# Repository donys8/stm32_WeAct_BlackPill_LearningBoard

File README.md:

# Learning Board STM32 WeAct Blackpill V2
Repository ini berisi desain Learning Board untuk STM32 WeAct Blackpill V2. Learning board ini dirancang untuk memudahkan pembelajaran dan eksperimen dengan mikrokontroler STM32, khususnya varian Blackpill dari WeAct.

## Deskripsi
Proyek ini mencakup file desain yang meliputi:

.kicad_pro : File proyek utama KiCad.

.kicad_sch : Schematic desain rangkaian.

.kicad_pcb : Layout PCB.

## Requirement
KiCad versi 7.x atau yang lebih baru

## 3D Preview

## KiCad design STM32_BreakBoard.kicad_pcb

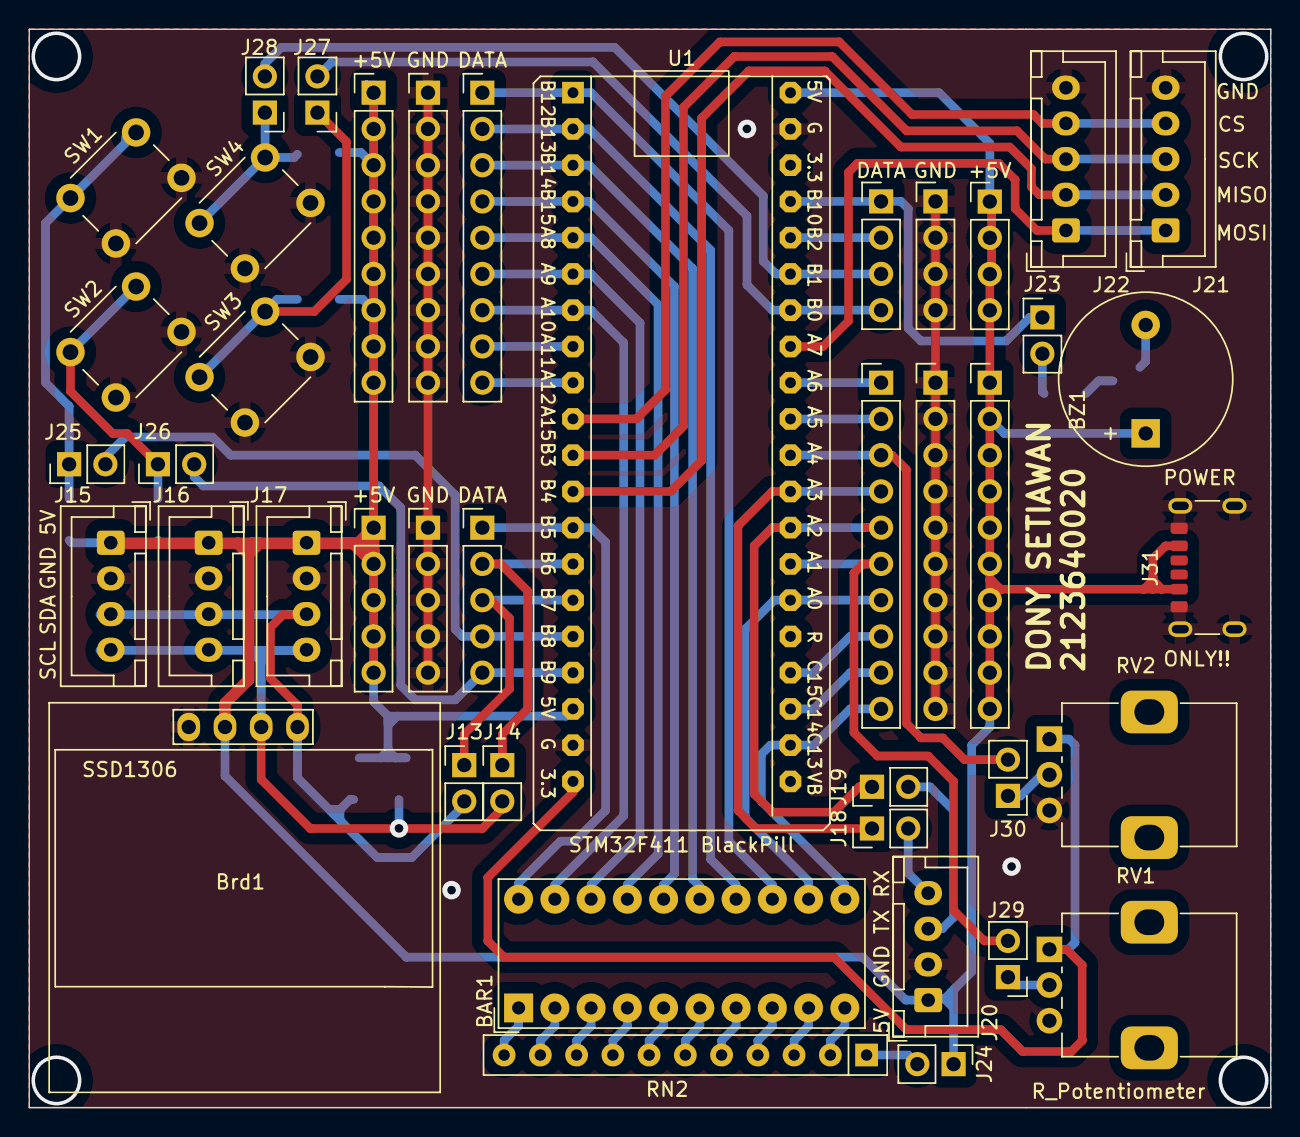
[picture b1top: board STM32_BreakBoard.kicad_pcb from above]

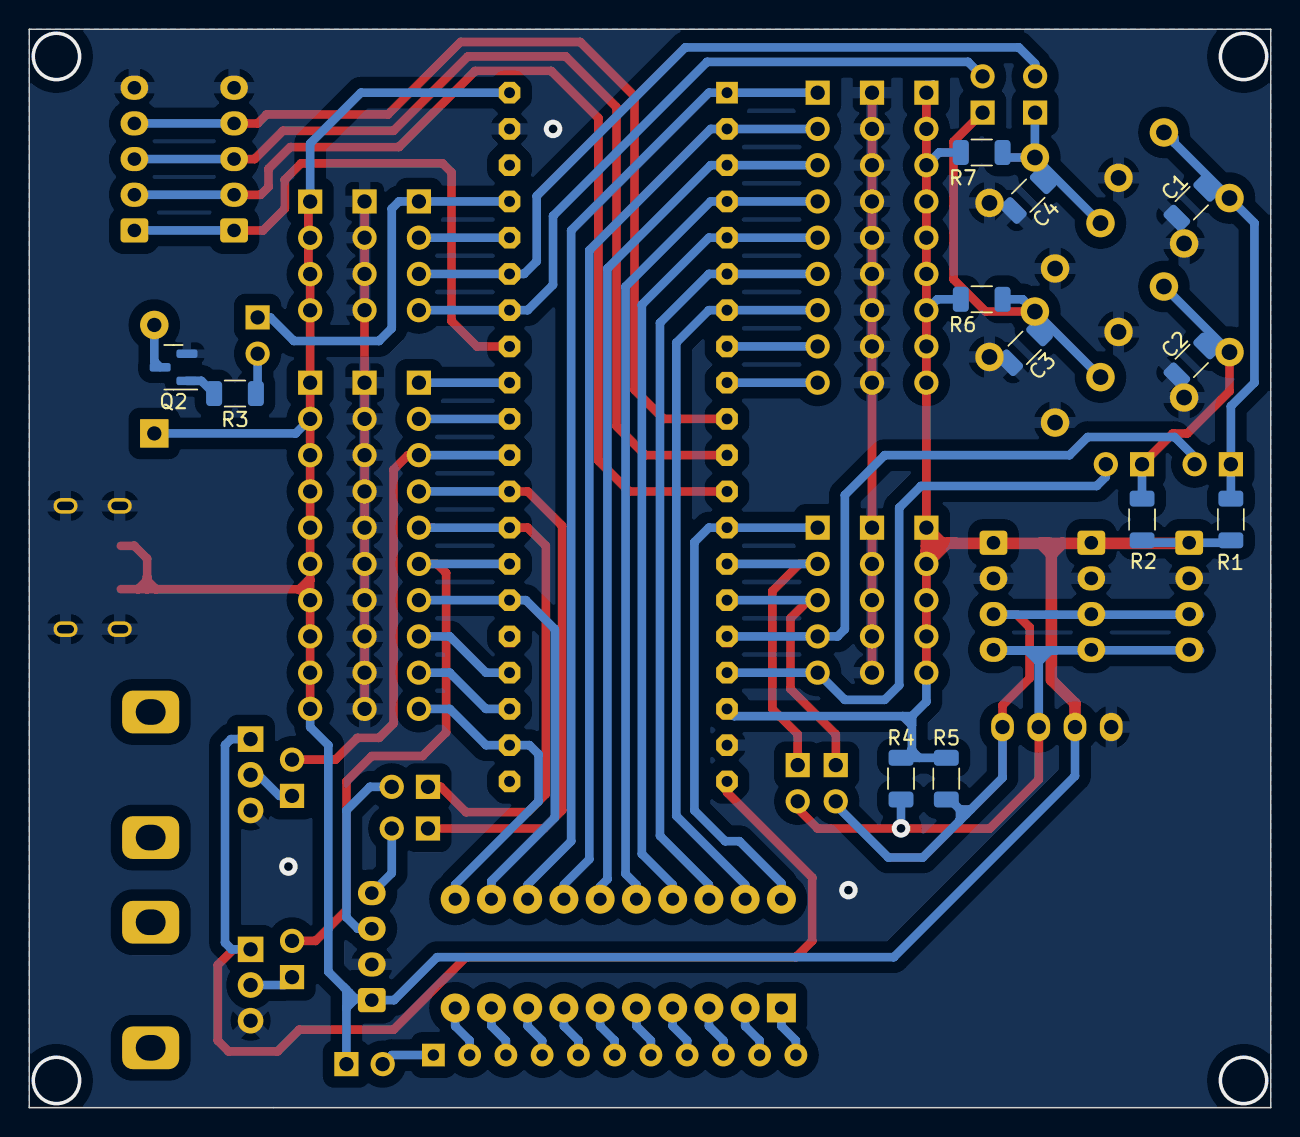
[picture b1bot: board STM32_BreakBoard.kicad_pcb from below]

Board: 2 copper layers, 87.0 x 75.6 mm, 54 parts (12 on the bottom side), 59 nets.

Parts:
BAR1: HDSP-4830_2; HDSP-4830
BZ1: Buzzer; Buzzer_12x9.5RM7.6
Brd1: SSD1306; 128x64OLED
C1, C2, C3, C4: C_Small; C_1206_3216Metric
J1: DATA; PinHeader_1x09_P2.54mm_Vertical
J2: DATA; PinHeader_1x05_P2.54mm_Vertical
J3: +5V; PinHeader_1x09_P2.54mm_Vertical
J4: +5V; PinHeader_1x05_P2.54mm_Vertical
J5: GND; PinHeader_1x09_P2.54mm_Vertical
J6: GND; PinHeader_1x05_P2.54mm_Vertical
J7: DATA; PinHeader_1x04_P2.54mm_Vertical
J8: DATA; PinHeader_1x10_P2.54mm_Vertical
J9: +5V; PinHeader_1x04_P2.54mm_Vertical
J10: +5V; PinHeader_1x10_P2.54mm_Vertical
J11: GND; PinHeader_1x04_P2.54mm_Vertical
J12: GND; PinHeader_1x10_P2.54mm_Vertical
J13, J14, J18, J19, J23, J24, J25, J26, J27, J28, J29, J30: Conn_01x02; PinHeader_1x02_P2.54mm_Vertical
J15, J16, J17, J20: Conn_01x04; JST_XH_B4B-XH-A_1x04_P2.50mm_Vertical
J21, J22: Conn_01x05; JST_XH_B5B-XH-A_1x05_P2.50mm_Vertical
J31: USB_C_Receptacle_PowerOnly_6P; USB_C_Receptacle_GCT_USB4125-xx-x_6P_TopMnt_Horizontal
Q2: Q_PMOS_GSD; SOT-23
R1, R2, R6, R7: 10k; R_1206_3216Metric
R3: 150; R_1206_3216Metric
R4, R5: 4k7; R_1206_3216Metric
RN2: R_Network10; R_Array_SIP11
RV1, RV2: R_Potentiometer; Potentiometer_Alps_RK09K_Single_Vertical
SW1, SW2, SW3, SW4: SW_Push_Dual; SW_PUSH_6mm
U1: STM32F411 BlackPill; STM32F411_Black_Pill

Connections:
+3V3: RV1.1, RV2.1, U1.20 (3.3V)
+5V: BZ1.1 (-), Brd1.2 (VCC), J3.1, J3.2, J3.3, J3.4, J3.5, J3.6, J3.7, J3.8, J3.9, J4.1, J4.2, J4.3, J4.4, J4.5, J9.1, J9.2, J9.3, J9.4, J10.1, J10.2, J10.3, J10.4, J10.5, J10.6, J10.7, J10.8, J10.9, J10.10, J15.1, J16.1, J17.1, J20.1, J24.1, J31.A9 (VBUS), J31.B9 (VBUS), R1.1, R2.1, R4.1, R5.1, R6.1, R7.1, U1.18 (5V), U1.40 (5V)
A0: BAR1.12 (K), J8.7, U1.26 (A0)
A1: J8.6, J29.2, U1.27 (A1)
A2: J8.5, J19.1, U1.28 (A2)
A3: J8.4, J18.1, U1.29 (A3)
A4: J8.3, J30.2, U1.30 (A4)
A5: J8.2, U1.31 (A5)
A6: J8.1, U1.32 (A6)
A7: J21.1, J22.1, U1.33 (A7)
A8: BAR1.17 (K), J1.5, U1.5 (A8)
A9: BAR1.18 (K), J1.6, U1.6 (A9)
A10: BAR1.19 (K), J1.7, U1.7 (A10)
A11: J1.8, U1.8 (A11)
A12: J1.9, U1.9 (A12)
A15: J21.4, J22.4, U1.10 (A15)
B0: J7.4, J27.2, U1.34 (B0)
B1: J7.3, J28.2, U1.35 (B1)
B2: J7.2, U1.36 (B2)
B3: J21.3, J22.3, U1.11 (B3)
B4: J21.2, J22.2, U1.12 (B4)
B5: BAR1.20 (K), J2.1, U1.13 (B5)
B6: J2.2, J14.1, U1.14 (B6)
B7: J2.3, J13.1, U1.15 (B7)
B8: J2.4, J25.2, U1.16 (B8)
B9: J2.5, J26.2, U1.17 (B9)
B10: J7.1, J23.1, U1.37 (B10)
B12: BAR1.13 (K), J1.1, U1.1 (B12)
B13: BAR1.14 (K), J1.2, U1.2 (B13)
B14: BAR1.15 (K), J1.3, U1.3 (B14)
B15: BAR1.16 (K), J1.4, U1.4 (B15)
BUZ: J23.2, R3.1
C13: BAR1.11 (K), J8.10, U1.22 (C13)
C14: J8.9, U1.23 (C14)
C15: J8.8, U1.24 (C15)
GND: Brd1.1 (GND), C1.2, C2.2, C3.2, C4.2, J5.1, J5.2, J5.3, J5.4, J5.5, J5.6, J5.7, J5.8, J5.9, J6.1, J6.2, J6.3, J6.4, J6.5, J11.1, J11.2, J11.3, J11.4, J12.1, J12.2, J12.3, J12.4, J12.5, J12.6, J12.7, J12.8, J12.9, J12.10, J15.2, J16.2, J17.2, J20.2, J21.5, J22.5, J31.A12 (GND), J31.B12 (GND), J31.S1 (SHIELD), Q2.2 (S), RV1.3, RV2.3, SW1.2, SW2.2, SW3.2, SW4.2, U1.19 (G), U1.39 (G)
unnamed: BZ1.2 (+), Q2.3 (D)
unnamed: J24.2, RN2.1 (common)
unnamed: J29.1, RV1.2
unnamed: J30.1, RV2.2
unnamed: Q2.1 (G), R3.2
unnamed: BAR1.10 (A), RN2.2 (R1)
unnamed: BAR1.9 (A), RN2.3 (R2)
unnamed: BAR1.8 (A), RN2.4 (R3)
unnamed: BAR1.7 (A), RN2.5 (R4)
unnamed: BAR1.6 (A), RN2.6 (R5)
unnamed: BAR1.5 (A), RN2.7 (R6)
unnamed: BAR1.4 (A), RN2.8 (R7)
unnamed: BAR1.3 (A), RN2.9 (R8)
unnamed: BAR1.2 (A), RN2.10 (R9)
unnamed: BAR1.1 (A), RN2.11 (R10)
PB1: C1.1, J25.1, R1.2, SW1.1
PB2: C2.1, J26.1, R2.2, SW2.1
PB3: C3.1, J27.1, R6.2, SW3.1
PB4: C4.1, J28.1, R7.2, SW4.1
RX: J18.2, J20.4
SCL: Brd1.3 (SCL), J14.2, J15.4, J16.4, J17.4, R4.2
SDA: Brd1.4 (SDA), J13.2, J15.3, J16.3, J17.3, R5.2
TX: J19.2, J20.3

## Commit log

2025-02-15 Add files via upload
    Schematic diagram
2025-02-15 3D Preview
